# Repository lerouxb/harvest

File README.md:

Harvest
===

A super low power energy-harvesting wifi temperature, humidity and voltage logger plus timelapse camera.

Very much a work in progress.

See https://lerouxb.co/2021/05/13/energy-harvesting-wifi.html for more details.

tl;dr
---

5.5V solar panel charges a 5.5V or 6V multi-farad supercapacitor. An attiny 1614 (could be smaller flash or pin count, could be 0 series as well - this is just what I had on hand) is connected straight to the supercapacitor. It measures its own supply voltage. If that is > 3.6V it powers a esp32 cam through a p-channel mosfet and 350mv dropout linear regulator. The esp32 cam reads a DHT22 to get temperature and humidity and asks the attiny for the supply voltage over i2c. It then connects to wifi and publishes those three values to an MQTT broker. Then it asks the attiny over i2c to cut the power. The attiny sleeps almost all the time. It just wakes up every second from the RTC and also when its i2c address matches. If 10 seconds passes without the esp32 signalling that it is done it will also cut the power as a failsafe just in case it is stuck. Every 60 seconds if the supply voltage is high enough it powers up the esp32 again and the cycle starts over.

Why an esp32 cam? So I can also use it to periodically take pictures and assemble them into a timelapse on the server.

Since the attiny is running at nominally 5V-ish and the esp32 at a regulated 3.3V, there's a [level shifter](https://cdn-shop.adafruit.com/datasheets/an97055.pdf) for the i2c bus.

The server also has an MQTT subscriber that stores the values in a mongo database that we can then pull out and graph.

An obvious optimisation would be to not even bother turning the esp32 on or taking pictures after sunset and before sunrise.

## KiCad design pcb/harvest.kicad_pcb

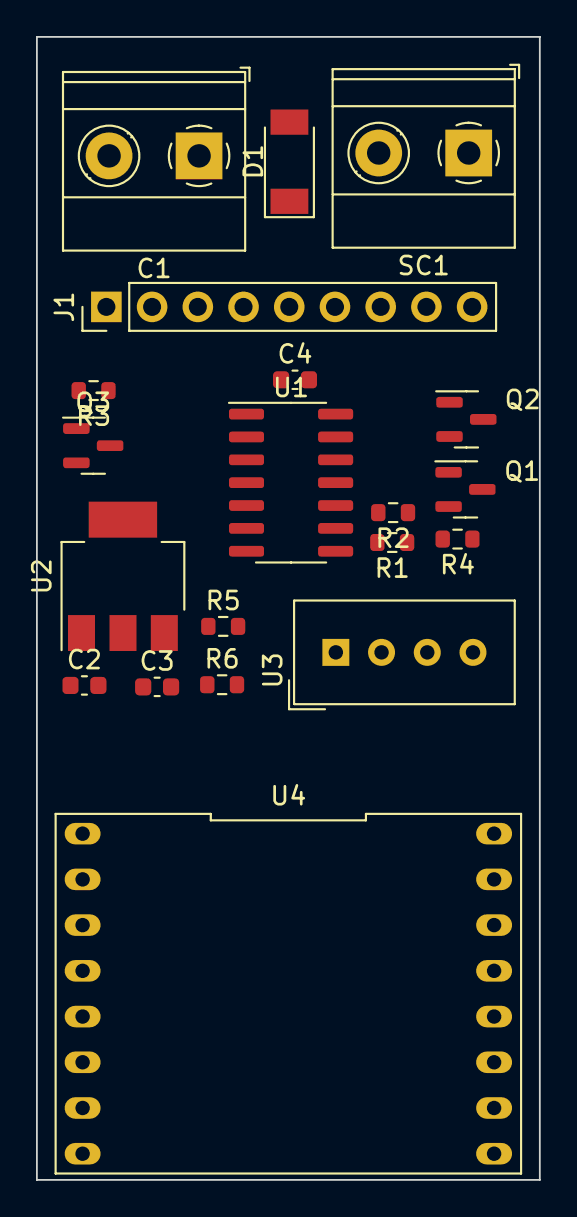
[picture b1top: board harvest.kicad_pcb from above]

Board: 2 copper layers, 27.9 x 63.5 mm, 20 parts (0 on the bottom side), 17 nets, no tracks yet.

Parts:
C1: 5.5V / 2.5F; TerminalBlock_Phoenix_MKDS-1,5-2_1x02_P5.00mm_Horizontal
C2: 4.7uF; C_0603_1608Metric
C3: 1uF; C_0603_1608Metric
C4: 100n; C_0603_1608Metric
D1: D_Schottky; D_SOD-128
J1: Conn_01x09; PinHeader_1x09_P2.54mm_Vertical
Q1, Q2: DMN6140L; SOT-23
Q3: DMG2301L; SOT-23
R1, R2, R3, R4, R5, R6: 10k; R_0603_1608Metric
SC1: Solar_Cells; TerminalBlock_Phoenix_MKDS-1,5-2_1x02_P5.00mm_Horizontal
U1: ATtiny1614-SS; SOIC-14_3.9x8.7mm_P1.27mm
U2: MCP1825S; SOT-223-3_TabPin2
U3: DHT11; Aosong_DHT11_5.5x12.0_P2.54mm
U4: esp32-cam

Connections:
+3V3: C3.1, J1.2, Q1.1 (G), Q2.1 (G), R4.1, R5.1, R6.1, U2.3 (VO), U3.1 (VCC), U4.16 (3.3V)
+5V: C1.1, C4.1, D1.1 (K), J1.1, Q3.3 (D), R1.1, R2.1, R3.1, U1.1 (VCC)
ATTINY_RX: J1.6, U1.12 (PA2)
ATTINY_SCL: Q2.3 (D), R2.2, U1.9 (PB0)
ATTINY_SDA: Q1.3 (D), R1.2, U1.8 (PB1)
ATTINY_TX: J1.7, U1.11 (PA1)
ESP32_RX: J1.8, U4.11 (GPIO_3_/_RXD)
ESP32_SCL: Q2.2 (S), R6.2, U4.3 (GPIO_12)
ESP32_SDA: Q1.2 (S), R5.2, U4.4 (GPIO_13)
ESP32_TX: J1.9, U4.10 (GPIO_1_/_TXD)
GND: C1.2, C2.2, C3.2, C4.2, J1.5, SC1.2 (-), U1.14 (GND), U2.2 (GND), U3.4 (GND), U4.2 (GND), U4.9 (GND), U4.13 (GND)
GPIO_0: J1.4, U4.14 (GPIO_0)
unnamed: C2.1, Q3.2 (S), U2.1 (VI)
unnamed: D1.2 (A), SC1.1 (+)
unnamed: Q3.1 (G), R3.2, U1.3 (PA5)
unnamed: R4.2, U3.2 (IO), U4.5 (GPIO_15)
UPDI: J1.3, U1.10 (~RESET~/PA0)

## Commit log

2021-05-29 talk about the level shifter
